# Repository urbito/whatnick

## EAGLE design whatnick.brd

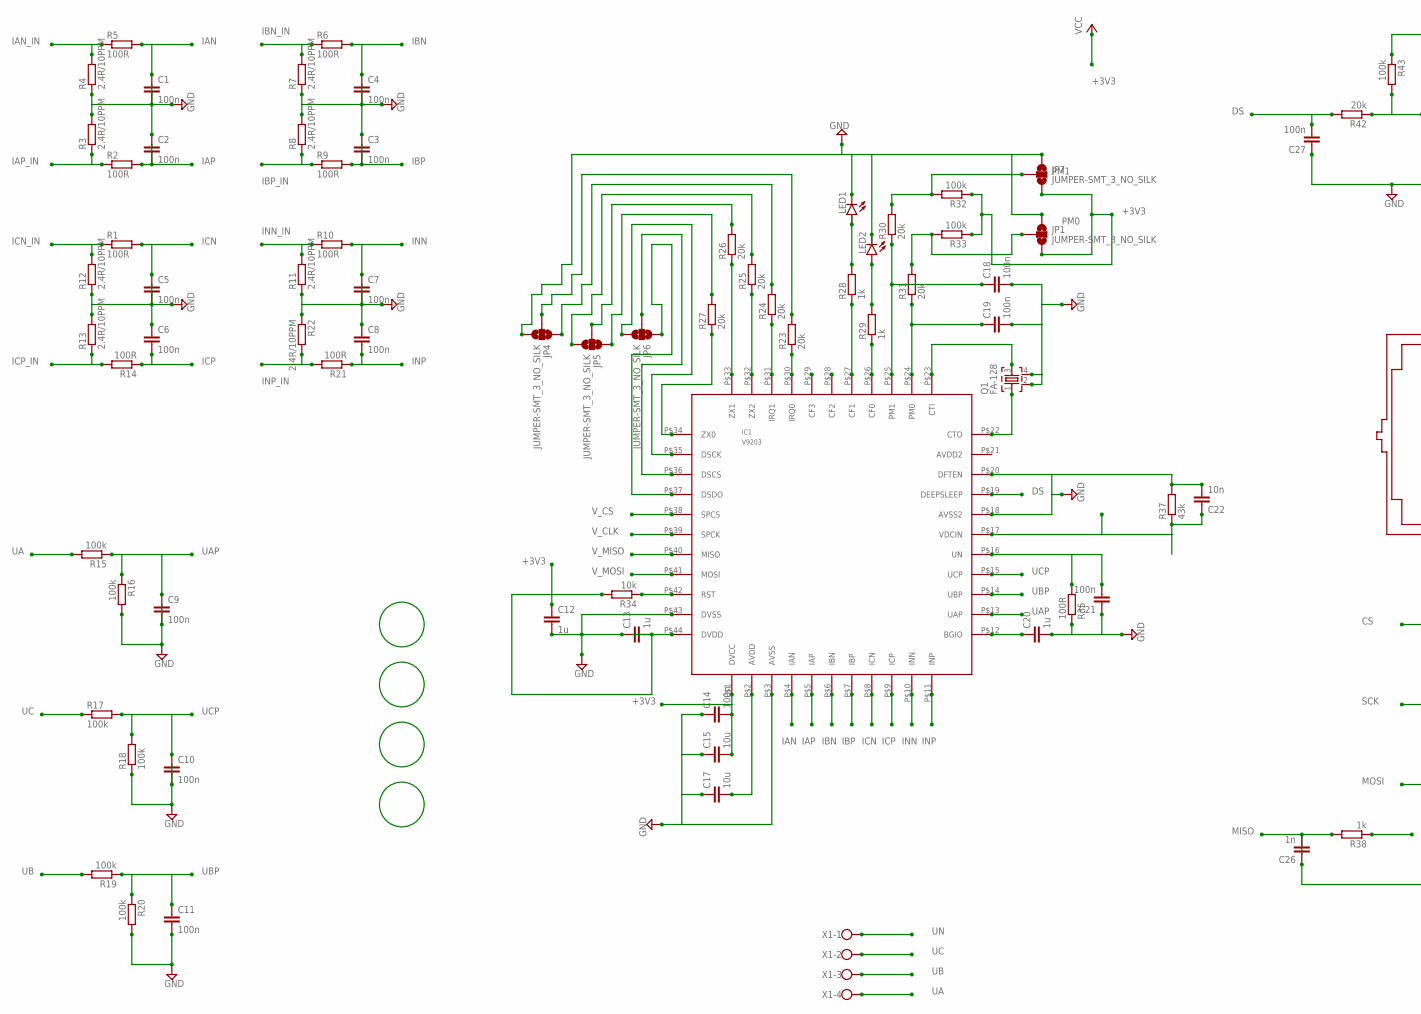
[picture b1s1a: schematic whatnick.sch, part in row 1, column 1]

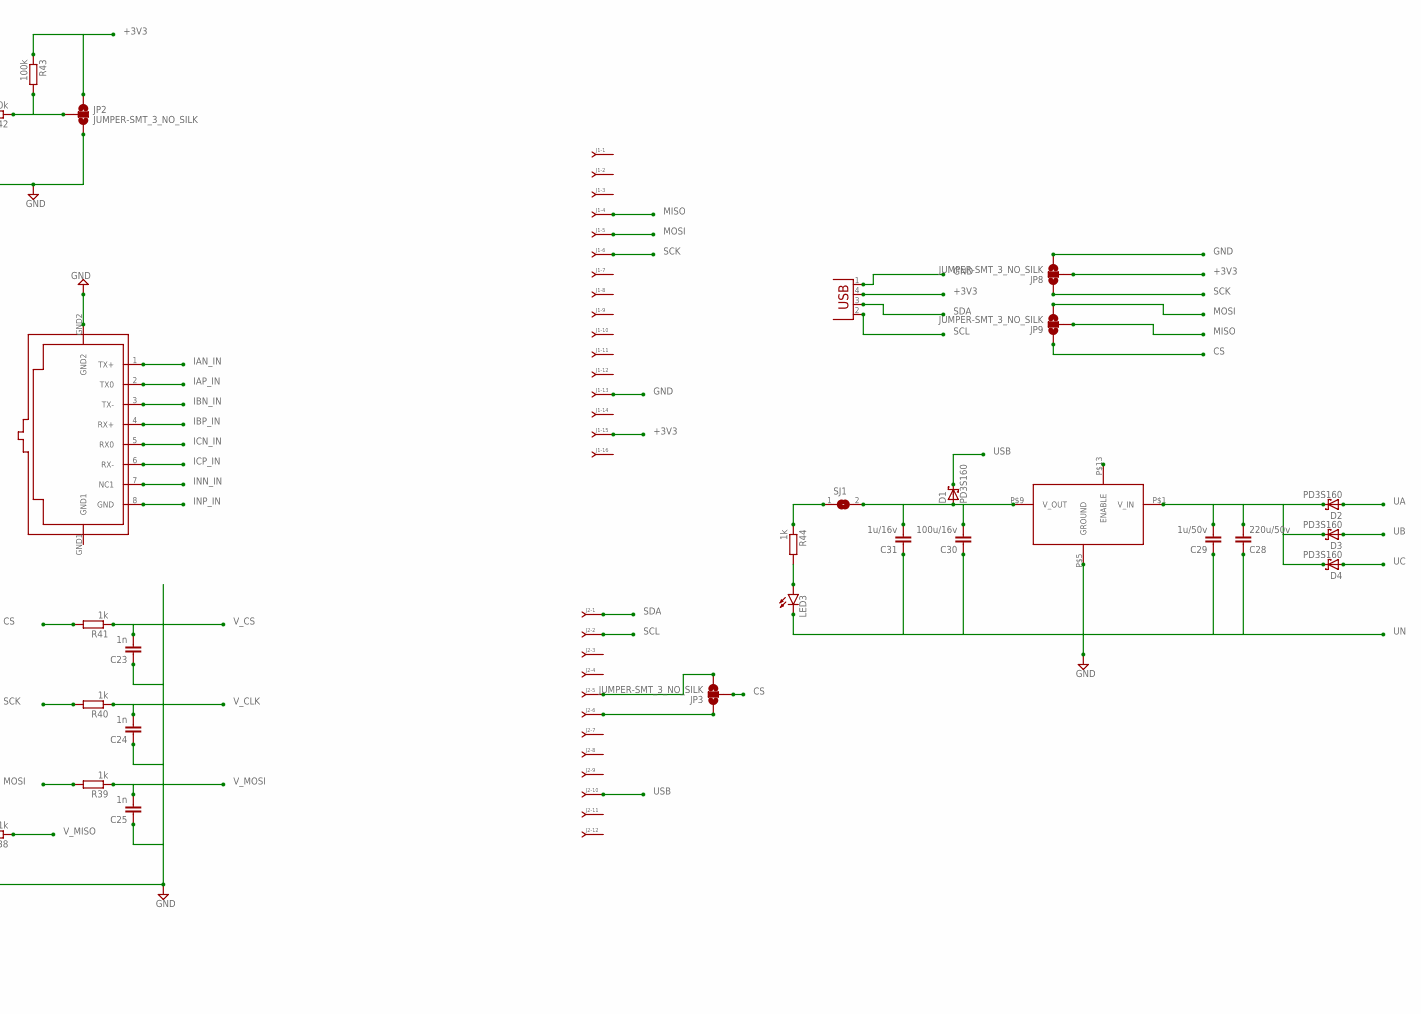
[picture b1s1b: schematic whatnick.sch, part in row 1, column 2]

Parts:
C1, C2, C3, C4, C5, C6, C7, C8, C9, C10, C11, C14, C18, C19, C21, C27: 100n; C0402
C12, C13, C20: 1u; C0402
C15, C17: 10u; C0402
C22: 10n; C0402
C23, C24, C25, C26: 1n; C0402
C28: 220u/50v; C0402
C29: 1u/50v; C0402
C30: 100u/16v; C0402
C31: 1u/16v; C0402
D1, D2, D3, D4: PD3S160; POWERDI323
IC1: V9203; 44LQFP
J1: J-16-SIP-100; SIP-100-16
J2: J-12-SIP-100; SIP-100-12
JP1, JP2, JP3, JP4, JP5, JP6, JP7, JP8, JP9: JUMPER-SMT_3_NO_SILK; SMT-JUMPER_3_NO_SILK
LED1, LED2, LED3: LEDCHIPLED-0603-TTW; CHIPLED-0603-TTW
Q1: FA-128
R1, R2, R5, R6, R9, R10, R14, R21, R35: 100R; R0402
R3, R4, R7, R8, R11, R12, R13, R22: 2.4R/10PPM; R0402
R15, R17, R19: 100k; R1206
R16, R18, R20, R32, R33, R43: 100k; R0402
R23, R24, R25, R26, R27, R30, R31, R42: 20k; R0402
R28, R29, R38, R39, R40, R41, R44: 1k; R0402
R34: 10k; R0402
R37: 43k; R0402
SJ1: SJW
U$1: RJ45-TRAFO
U$2: ROF-78EXX-0.5SMD
X1: W237-4
X5: USB-JST-2MM-SMT; S4B-PH

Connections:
+3V3: C12.1, C13.2, C14.2, C15.2, C22.1, IC1.P$1 (DVCC), IC1.P$17 (VDCIN), IC1.P$44 (DVDD), J1.15, JP1.3, JP2.1, JP7.3, JP8.2, R32.1, R33.1, R34.2, R37.1, R43.1, X5.4 (VBUS)
CS: JP3.2, JP9.1, R41.2
DS: C27.2, IC1.P$19 (DEEPSLEEP), R42.2
DSCK: IC1.P$35 (DSCK), JP6.3
DSCS: IC1.P$36 (DSCS), JP6.2
DSDO: IC1.P$37 (DSDO), JP6.1
GND: C1.2, C2.1, C3.1, C4.2, C5.2, C6.1, C7.2, C8.1, C9.2, C10.2, C11.2, C12.2, C13.1, C14.1, C15.1, C17.1, C18.2, C19.2, C20.2, C21.1, C22.2, C23.1, C24.1, C25.1, C26.1, C27.1, IC1.P$3 (AVSS), IC1.P$18 (AVSS2), IC1.P$20 (DFTEN), IC1.P$43 (DVSS), J1.13, JP1.1, JP2.3, JP4.3, JP7.1, JP8.3, LED1.C@1 (CATHODE), LED2.C@1 (CATHODE), Q1.2, Q1.4, R3.2, R4.1, R7.1, R8.2, R11.1, R12.1, R13.2, R16.2, R18.1, R20.2, R22.1, R35.1, R37.2, X5.1 (GND)
GND2: U$1.GND2
IAN: C1.1, IC1.P$4 (IAN), R5.2
IAN_IN: R4.2, R5.1, U$1.1 (TX+)
IAP: C2.2, IC1.P$5 (IAP), R2.2
IAP_IN: R2.1, R3.1, U$1.2 (TX0)
IBN: C4.1, IC1.P$6 (IBN), R6.2
IBN_IN: R6.1, R7.2, U$1.3 (TX-)
IBP: C3.2, IC1.P$7 (IBP), R9.2
IBP_IN: R8.1, R9.1, U$1.4 (RX+)
ICN: C5.1, IC1.P$8 (ICN), R1.2
ICN_IN: R1.1, R12.2, U$1.5 (RX0)
ICP: C6.2, IC1.P$9 (ICP), R14.1
ICP_IN: R13.1, R14.2, U$1.6 (RX-)
INN: C7.1, IC1.P$10 (INN), R10.2
INN_IN: R10.1, R11.2, U$1.7 (NC1)
INP: C8.2, IC1.P$11 (INP), R21.1
INP_IN: R21.2, R22.2, U$1.8 (GND)
IRQ0: JP4.2, R23.2
IRQ1: JP4.1, R24.2
MISO: C26.2, J1.4, JP9.2, R38.2
MOSI: J1.5, JP9.3, R39.2
unnamed: LED3.A@1 (ANODE), R44.2
unnamed: JP2.2, R42.1, R43.2
unnamed: LED1.A@1 (ANODE), R28.2
unnamed: IC1.P$23 (CTI), Q1.3
unnamed: C20.1, IC1.P$12 (BGIO)
unnamed: LED2.A@1 (ANODE), R29.2
unnamed: IC1.P$22 (CTO), Q1.1
unnamed: IC1.P$34 (ZX0), R27.1
unnamed: C21.2, IC1.P$16 (UN), R35.2
unnamed: IC1.P$30 (IRQ0), R23.1
unnamed: IC1.P$31 (IRQ1), R24.1
unnamed: IC1.P$32 (ZX2), R25.1
unnamed: IC1.P$33 (ZX1), R26.1
unnamed: C19.1, IC1.P$24 (PM0), R31.1
unnamed: C18.1, IC1.P$25 (PM1), R30.1
unnamed: IC1.P$27 (CF1), R28.1
unnamed: IC1.P$26 (CF0), R29.1
unnamed: IC1.P$42 (RST), R34.1
unnamed: C17.2, IC1.P$2 (AVDD)
unnamed: J2.5, JP3.3
unnamed: C30.2, C31.2, D1.A, SJ1.2, U$2.P$9 (V_OUT)
unnamed: C28.2, C29.2, D2.C, D3.C, D4.C, U$2.P$1 (V_IN)
unnamed: J2.6, JP3.1
unnamed: R44.1, SJ1.1
PM0: JP1.2, R31.2, R33.2
PM1: JP7.2, R30.2, R32.2
SCK: J1.6, JP8.1, R40.2
SCL: J2.2, X5.2 (D+)
SDA: J2.1, X5.3 (D-)
UA: D2.A, R15.2, X1.4
UAP: C9.1, IC1.P$13 (UAP), R15.1, R16.1
UB: D3.A, R19.2, X1.3
UBP: C11.1, IC1.P$14 (UBP), R19.1, R20.1
UC: D4.A, R17.1, X1.2
UCP: C10.1, IC1.P$15 (UCP), R17.2, R18.2
UN: C28.1, C29.1, C30.1, C31.1, LED3.C@1 (CATHODE), U$2.P$5 (GROUND), X1.1
USB: D1.C, J2.10
V_CLK: C24.2, IC1.P$39 (SPCK), R40.1
V_CS: C23.2, IC1.P$38 (SPCS), R41.1
V_MISO: IC1.P$40 (MISO), R38.1
V_MOSI: C25.2, IC1.P$41 (MOSI), R39.1
ZX0: JP5.1, R27.2
ZX1: JP5.2, R26.2
ZX2: JP5.3, R25.2

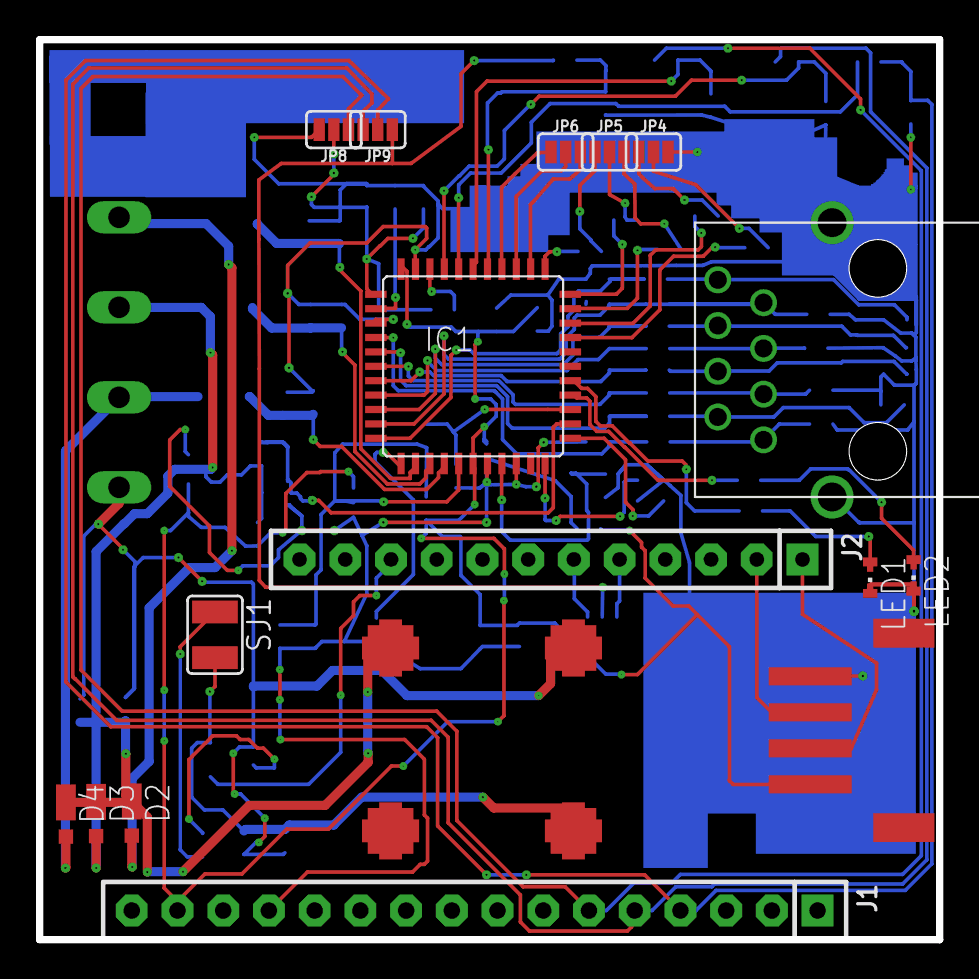
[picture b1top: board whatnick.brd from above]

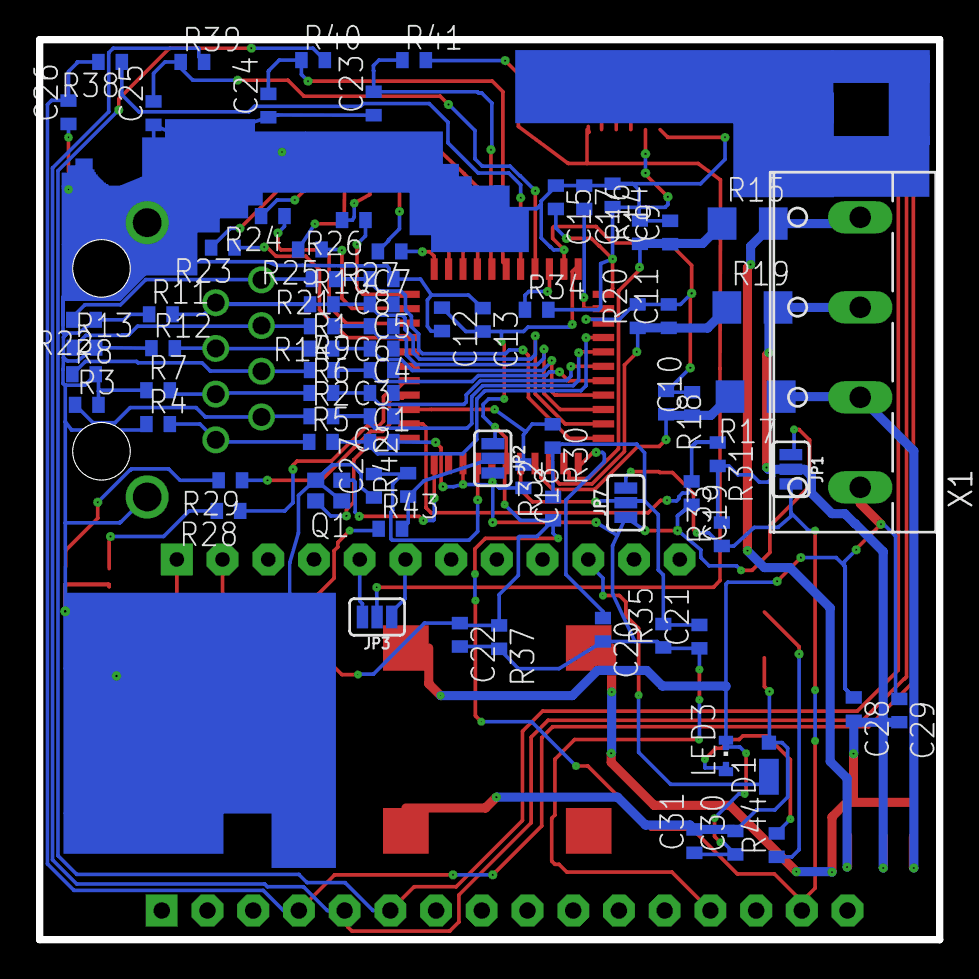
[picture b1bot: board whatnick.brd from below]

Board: 2 copper layers, 50.0 x 50.0 mm, 98 parts (81 on the bottom side), 71 nets.

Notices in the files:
parts and their libraries:
con-headers-jp: Copyright (C) 2004, Bob Starr (rtzaudio@mindspring.com)
DECADE-libraries20151104: Licensing: Creative Commons ShareAlike 4.0 International - https://creativecommons.org/licenses/by-sa/4.0
